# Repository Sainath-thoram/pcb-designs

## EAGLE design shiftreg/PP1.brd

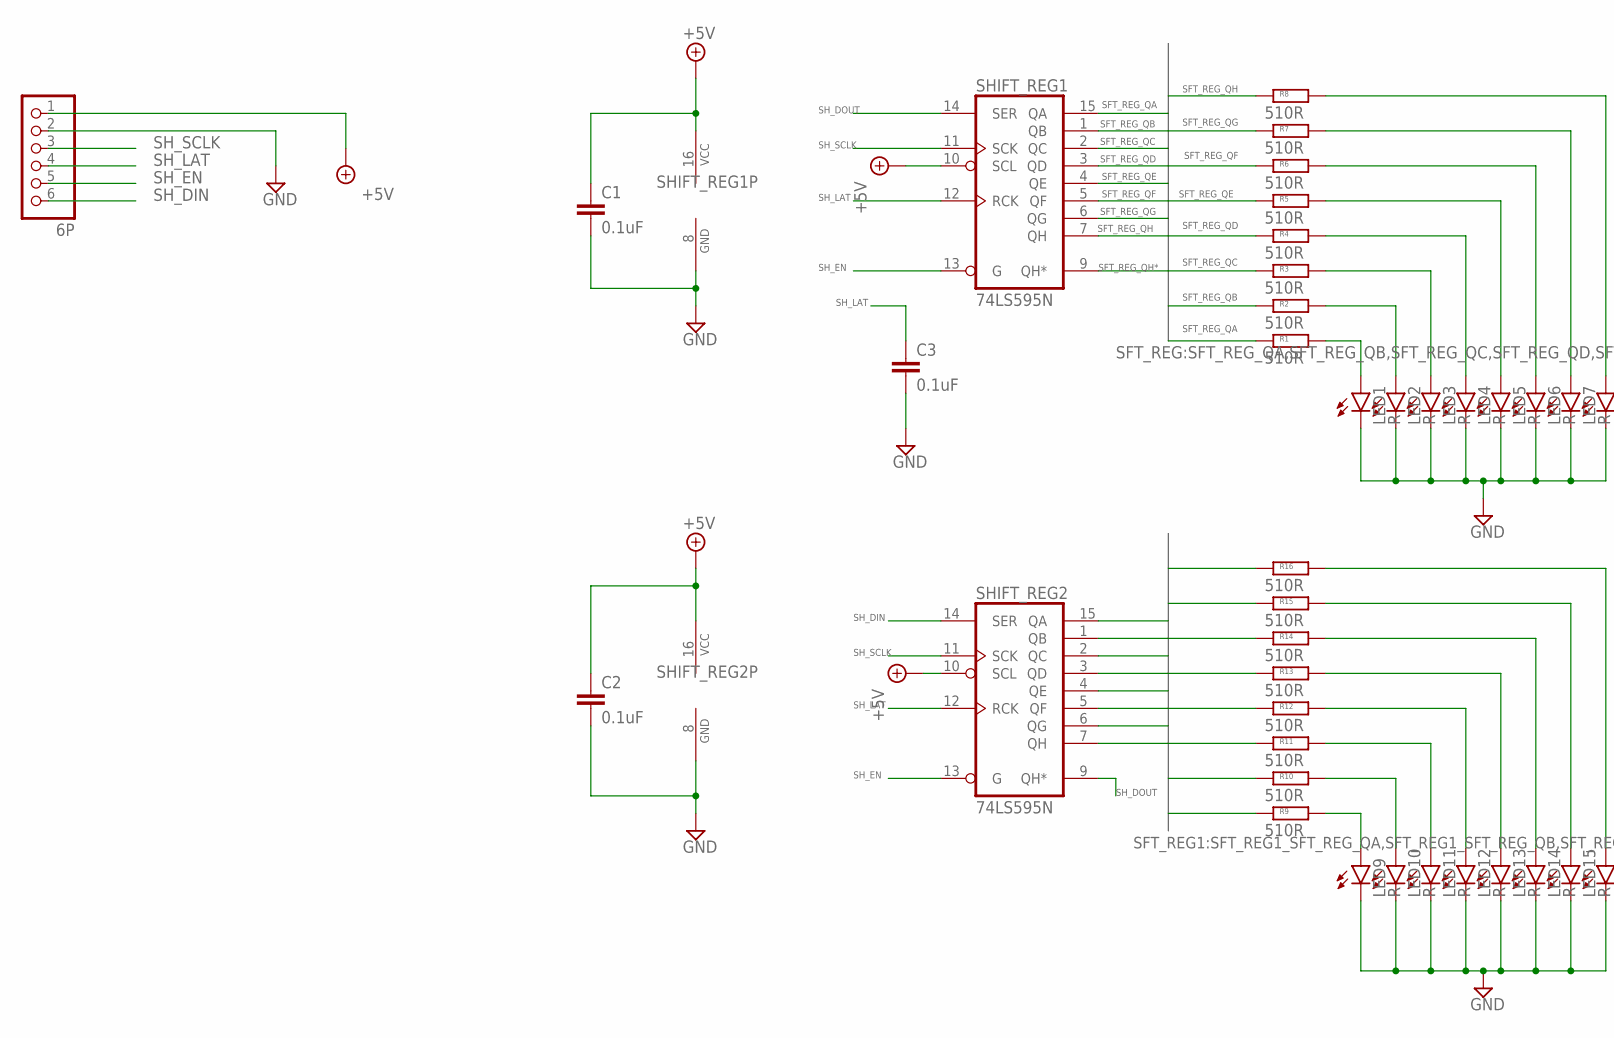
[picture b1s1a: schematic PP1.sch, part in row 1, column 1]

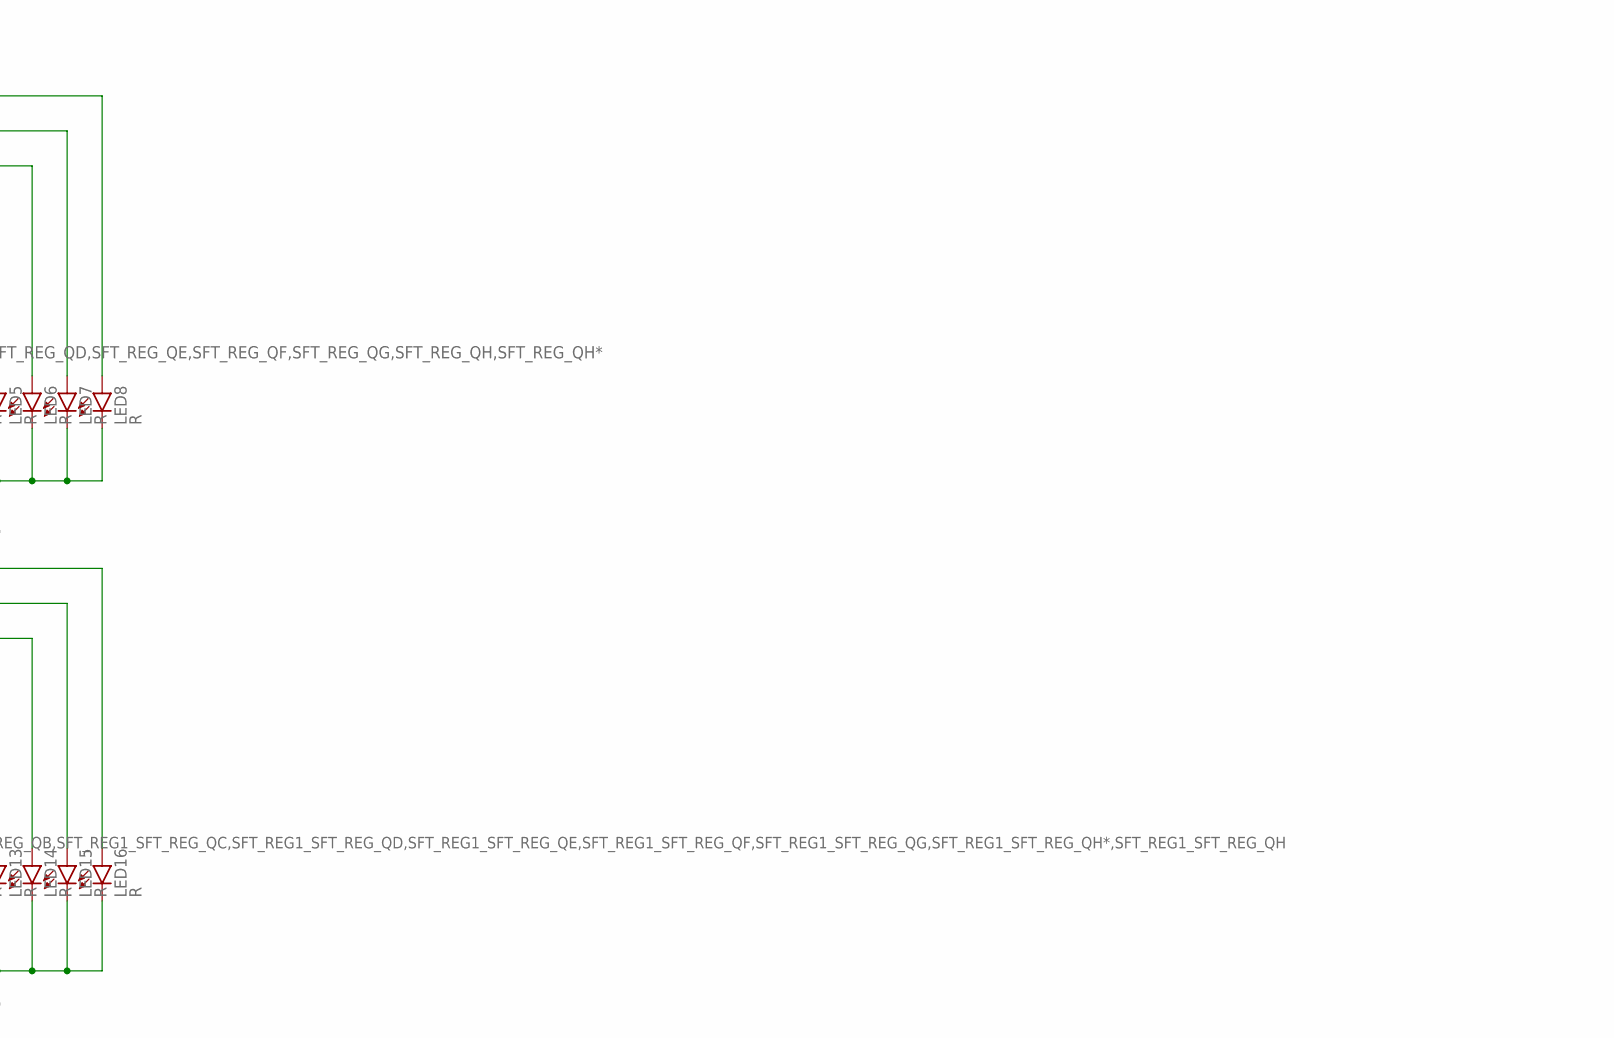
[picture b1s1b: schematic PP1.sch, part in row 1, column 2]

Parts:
C1, C2, C3: 0.1uF; C050-030X075
INPUT: 6P; 1X06/90
LED1, LED2, LED3, LED4, LED5, LED6, LED7, LED8, LED9, LED10, LED11, LED12, LED13, LED14, LED15, LED16: R; LED5MM
R1, R2, R3, R4, R5, R6, R7, R8, R9, R10, R11, R12, R13, R14, R15, R16: 510R; 0207/10
SHIFT_REG1, SHIFT_REG2: 74LS595N; DIL16

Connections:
+5V: C1.1, C2.1, INPUT.1, SHIFT_REG1.10 (SCL), SHIFT_REG1.16 (VCC), SHIFT_REG2.10 (SCL), SHIFT_REG2.16 (VCC)
GND: C1.2, C2.2, C3.2, INPUT.2, LED1.K (C), LED2.K (C), LED3.K (C), LED4.K (C), LED5.K (C), LED6.K (C), LED7.K (C), LED8.K (C), LED9.K (C), LED10.K (C), LED11.K (C), LED12.K (C), LED13.K (C), LED14.K (C), LED15.K (C), LED16.K (C), SHIFT_REG1.8 (GND), SHIFT_REG2.8 (GND)
unnamed: LED1.A, R1.2
unnamed: LED2.A, R2.2
unnamed: LED3.A, R3.2
unnamed: LED4.A, R4.2
unnamed: LED5.A, R5.2
unnamed: LED6.A, R6.2
unnamed: LED9.A, R9.2
unnamed: LED10.A, R10.2
unnamed: LED7.A, R7.2
unnamed: LED8.A, R8.2
unnamed: LED11.A, R11.2
unnamed: LED12.A, R12.2
unnamed: LED13.A, R13.2
unnamed: LED14.A, R14.2
unnamed: LED15.A, R15.2
unnamed: LED16.A, R16.2
SFT_REG1_SFT_REG_QA: R9.1, SHIFT_REG2.15 (QA)
SFT_REG1_SFT_REG_QB: R10.1, SHIFT_REG2.1 (QB)
SFT_REG1_SFT_REG_QC: R11.1, SHIFT_REG2.2 (QC)
SFT_REG1_SFT_REG_QD: R12.1, SHIFT_REG2.3 (QD)
SFT_REG1_SFT_REG_QE: R13.1, SHIFT_REG2.4 (QE)
SFT_REG1_SFT_REG_QF: R14.1, SHIFT_REG2.5 (QF)
SFT_REG1_SFT_REG_QG: R15.1, SHIFT_REG2.6 (QG)
SFT_REG1_SFT_REG_QH: R16.1, SHIFT_REG2.7 (QH)
SFT_REG_QA: R1.1, SHIFT_REG1.15 (QA)
SFT_REG_QB: R2.1, SHIFT_REG1.1 (QB)
SFT_REG_QC: R3.1, SHIFT_REG1.2 (QC)
SFT_REG_QD: R4.1, SHIFT_REG1.3 (QD)
SFT_REG_QE: R5.1, SHIFT_REG1.4 (QE)
SFT_REG_QF: R6.1, SHIFT_REG1.5 (QF)
SFT_REG_QG: R7.1, SHIFT_REG1.6 (QG)
SFT_REG_QH: R8.1, SHIFT_REG1.7 (QH)
SFT_REG_QH*: SHIFT_REG1.9 (QH*)
SH_DIN: INPUT.6, SHIFT_REG2.14 (SER)
SH_DOUT: SHIFT_REG1.14 (SER), SHIFT_REG2.9 (QH*)
SH_EN: INPUT.5, SHIFT_REG1.13 (G), SHIFT_REG2.13 (G)
SH_LAT: C3.1, INPUT.4, SHIFT_REG1.12 (RCK), SHIFT_REG2.12 (RCK)
SH_SCLK: INPUT.3, SHIFT_REG1.11 (SCK), SHIFT_REG2.11 (SCK)

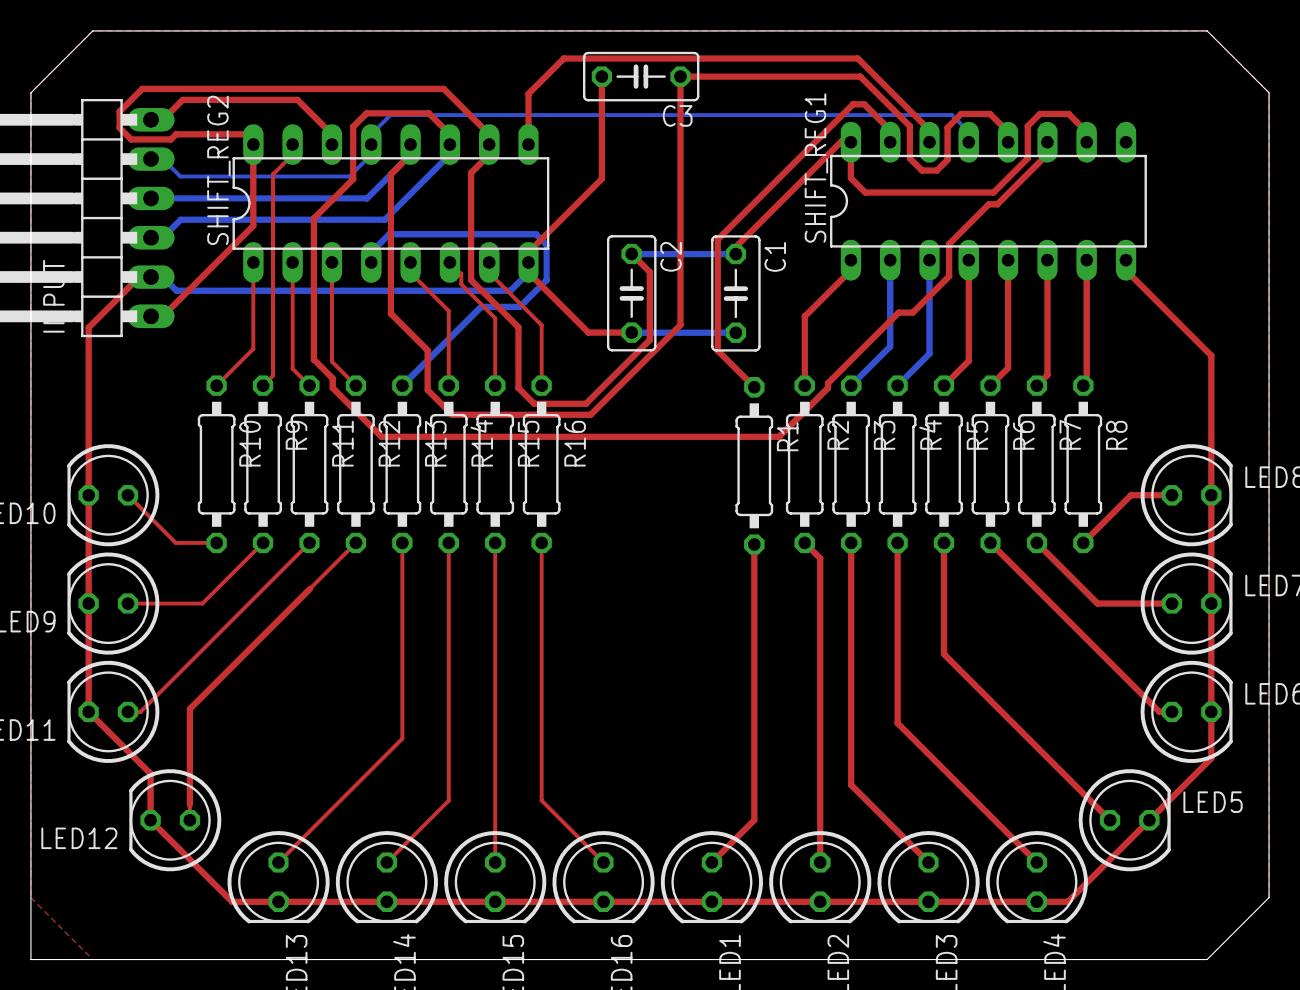
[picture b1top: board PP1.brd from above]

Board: 2 copper layers, 80.0 x 60.0 mm, 38 parts (0 on the bottom side), 39 nets.

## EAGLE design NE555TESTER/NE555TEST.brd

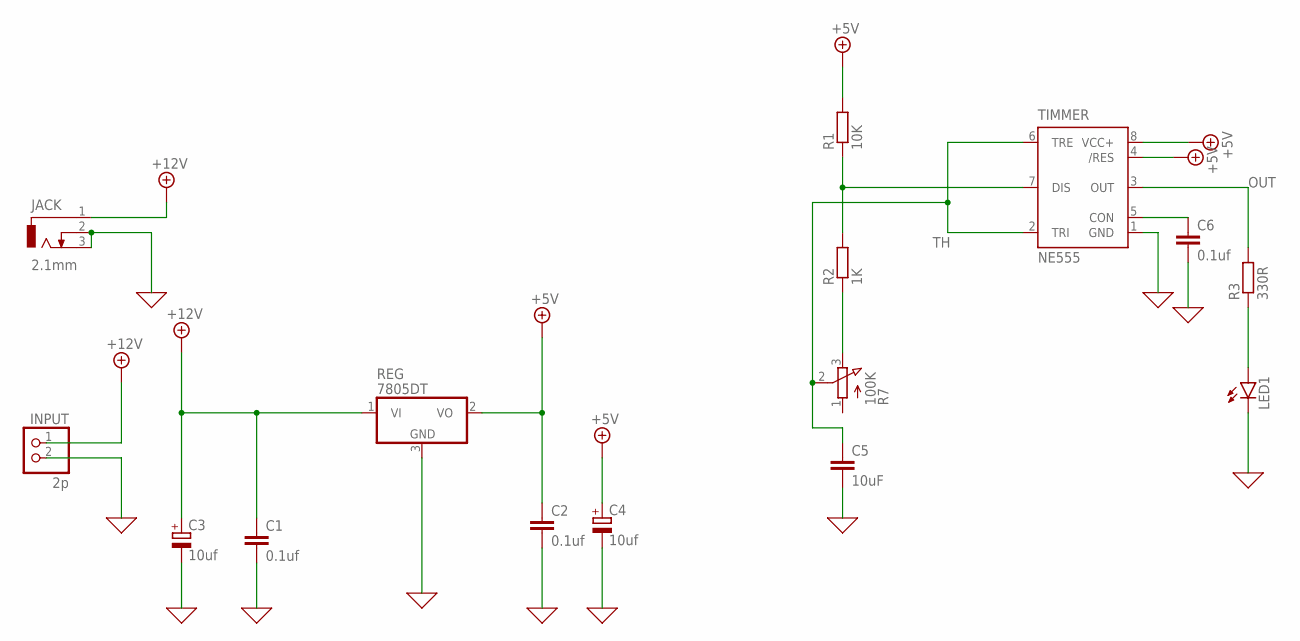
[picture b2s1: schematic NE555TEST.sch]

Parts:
C1, C2, C6: 0.1uf; C050-030X075
C3, C4: 10uf; E3,5-8
C5: 10uF; C050-030X075
INPUT: 2p; 1X02
JACK: 2.1mm; DCJ0202
LED1: LED3MM
R1: 10K; 0207/10
R2: 1K; 0207/10
R3: 330R; 0207/10
R7: 100K; 3RP/1610N
REG: 7805DT; TO252
TIMMER: NE555; DIL-08

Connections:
0: C1.2, C2.2, C3.-, C4.-, C5.2, C6.2, INPUT.2, JACK.2, JACK.3, LED1.K (C), REG.3 (GND), TIMMER.1 (GND)
+5V: C2.1, C4.+, R1.2, REG.2 (VO), TIMMER.4 (/RES), TIMMER.8 (VCC+)
+12V: C1.1, C3.+, INPUT.1, JACK.1, REG.1 (VI)
unnamed: C6.1, TIMMER.5 (CON)
unnamed: R1.1, R2.2, TIMMER.7 (DIS)
unnamed: R2.1, R7.3 (E)
unnamed: LED1.A, R3.1
OUT: R3.2, TIMMER.3 (OUT)
TH: C5.1, R7.2 (S), TIMMER.2 (TRI), TIMMER.6 (TRE)

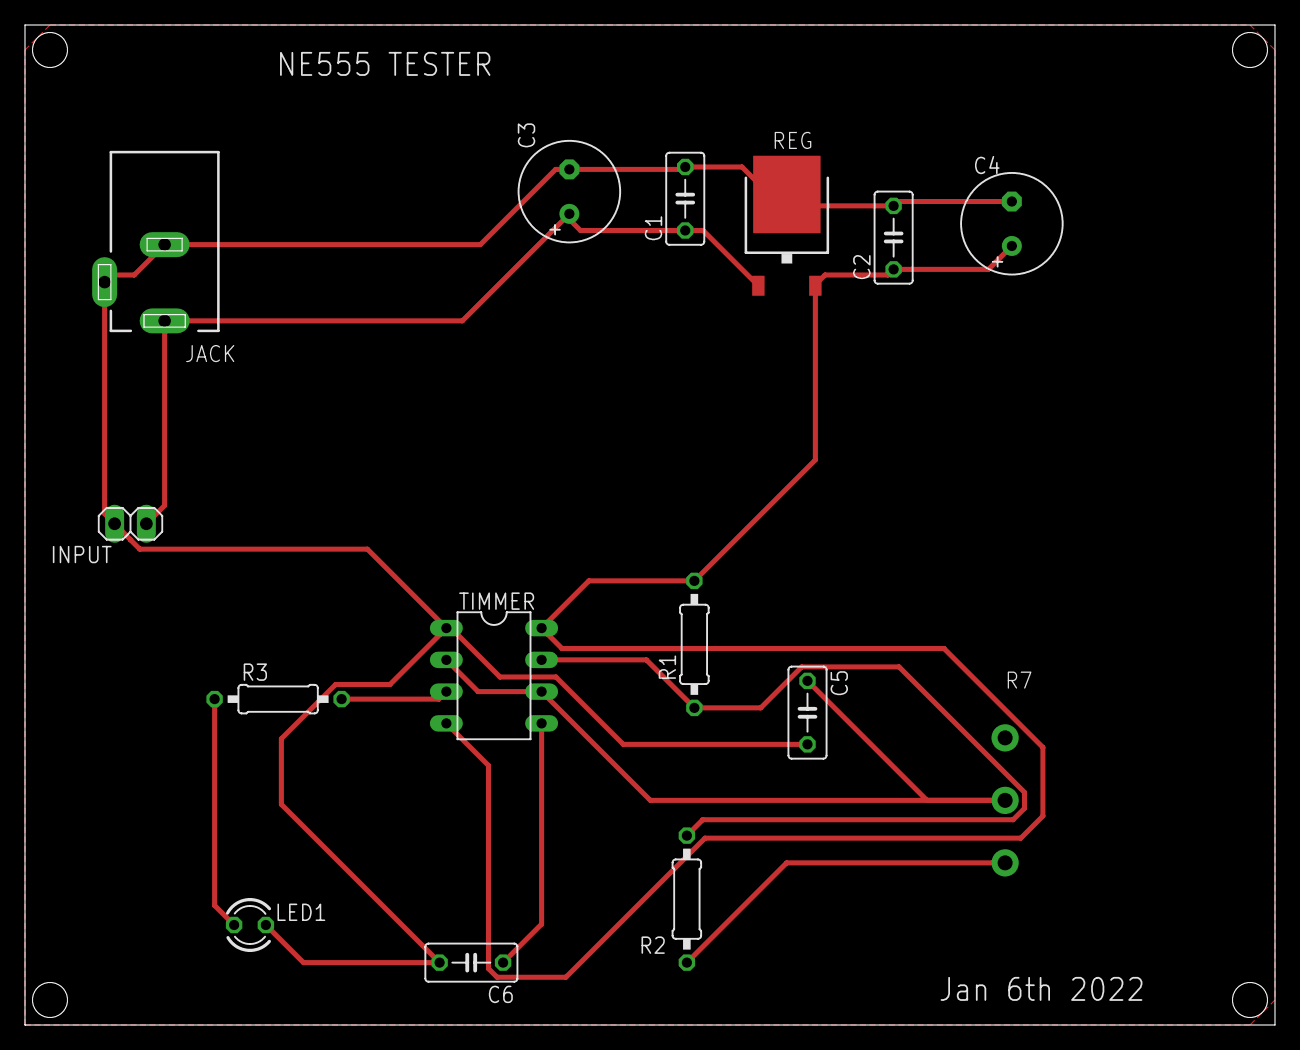
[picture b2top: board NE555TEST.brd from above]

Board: 2 copper layers, 100.0 x 80.0 mm, 15 parts (1 on the bottom side), 9 nets.

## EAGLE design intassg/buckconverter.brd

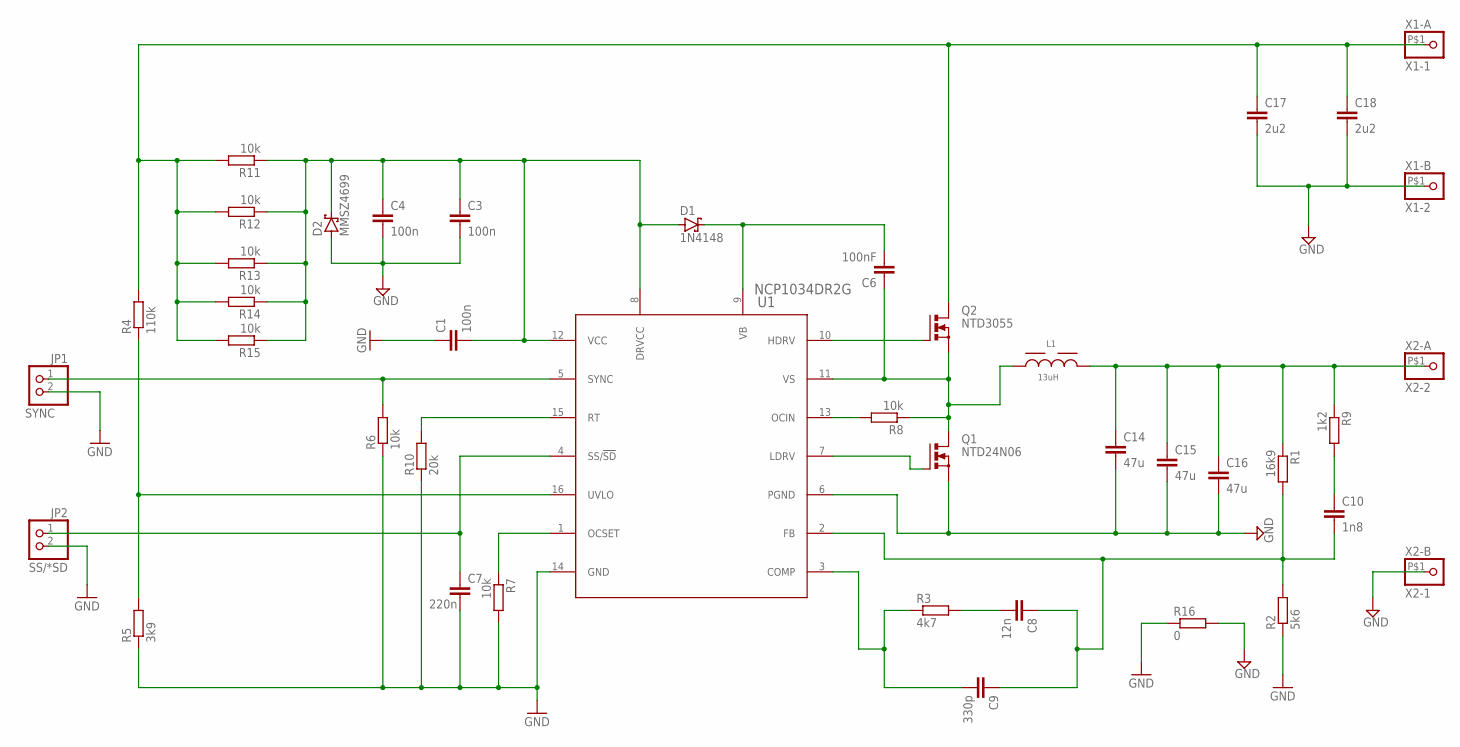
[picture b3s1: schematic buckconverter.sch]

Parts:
C1, C3, C4: 100n; C1206
C6: 100nF; C1206
C7: 220n; C1206
C8: 12n; C1206
C9: 330p; C1206
C10: 1n8; C1206
C14, C15, C16: 47u; C1210
C17, C18: 2u2; C1210
D1: 1N4148; SOT23
D2: MMSZ4699; SOT23
JP1: SYNC; 1X02
JP2: SS/*SD; 1X02
L1: 13uH; WE-HCI_1365
Q1: NTD24N06; TO220BV
Q2: NTD3055; TO220BV
R1: 16k9; R1206
R2: 5k6; R1206
R3: 4k7; R1206
R4: 110k; R1206
R5: 3k9; R1206
R6, R7, R8, R11, R12, R13, R14, R15: 10k; R1206
R9: 1k2; R1206
R10: 20k; R1206
R16: 0; R1206
U1: NCP1034DR2G; SOIC-16_ONS
X1-A: X1-1; 1X1-BIGPOGO
X1-B: X1-2; 1X1-BIGPOGO
X2-A: X2-2; 1X1-BIGPOGO
X2-B: X2-1; 1X1-BIGPOGO

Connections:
GND: C1.1, C3.2, C4.2, C7.2, C14.2, C15.2, C16.2, C17.2, C18.2, D2.1 (A), JP1.2, JP2.2, Q1.S, R2.1, R5.1, R6.1, R7.2, R10.1, R16.1, R16.2, U1.6 (PGND), U1.14 (GND), X1-B.P$1, X2-B.P$1
unnamed: R7.1, U1.1 (OCSET)
unnamed: C7.1, JP2.1, U1.4 (SS/!SD)
unnamed: R10.2, U1.15 (RT)
unnamed: JP1.1, R6.2, U1.5 (SYNC)
unnamed: Q1.G, U1.7 (LDRV)
unnamed: R8.2, U1.13 (OCIN)
unnamed: C6.1, L1.1, Q1.D, Q2.S, R8.1, U1.11 (VS)
unnamed: Q2.G, U1.10 (HDRV)
unnamed: C6.2, D1.3 (C), U1.9 (VB)
unnamed: C10.1, R9.2
unnamed: C8.2, R3.2
unnamed: C8.1, C9.1, C10.2, R1.2, R2.2, U1.2 (FB)
unnamed: C14.1, C15.1, C16.1, L1.2, R1.1, R9.1, X2-A.P$1
unnamed: C9.2, R3.1, U1.3 (COMP)
unnamed: C17.1, C18.1, Q2.D, R4.2, R11.2, R12.2, R13.2, R14.2, R15.2, X1-A.P$1
unnamed: R4.1, R5.2, U1.16 (UVLO)
unnamed: C1.2, C3.1, C4.1, D1.1 (A), D2.3 (C), R11.1, R12.1, R13.1, R14.1, R15.1, U1.8 (DRVCC), U1.12 (VCC)

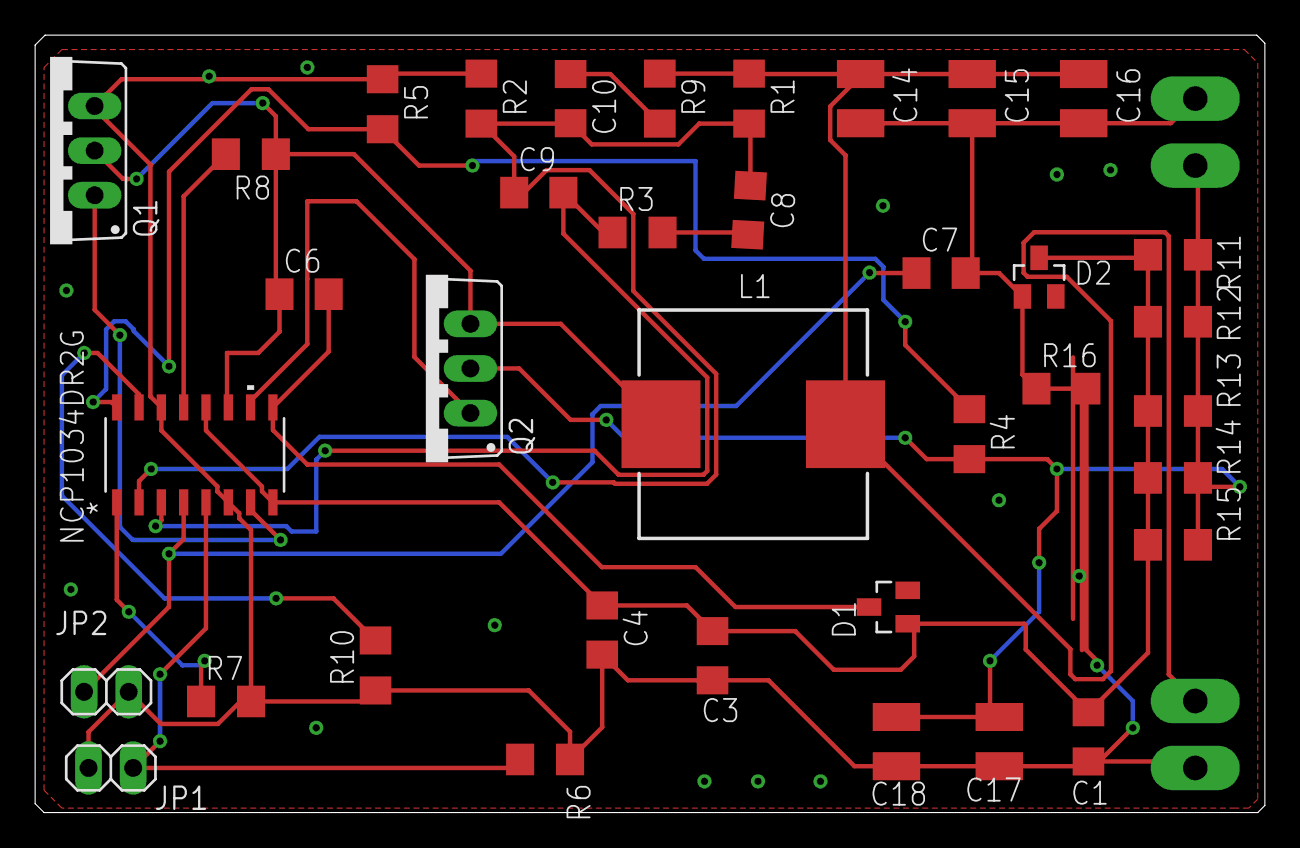
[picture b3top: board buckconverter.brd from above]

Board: 2 copper layers, 70.0 x 44.3 mm, 41 parts (0 on the bottom side), 18 nets.

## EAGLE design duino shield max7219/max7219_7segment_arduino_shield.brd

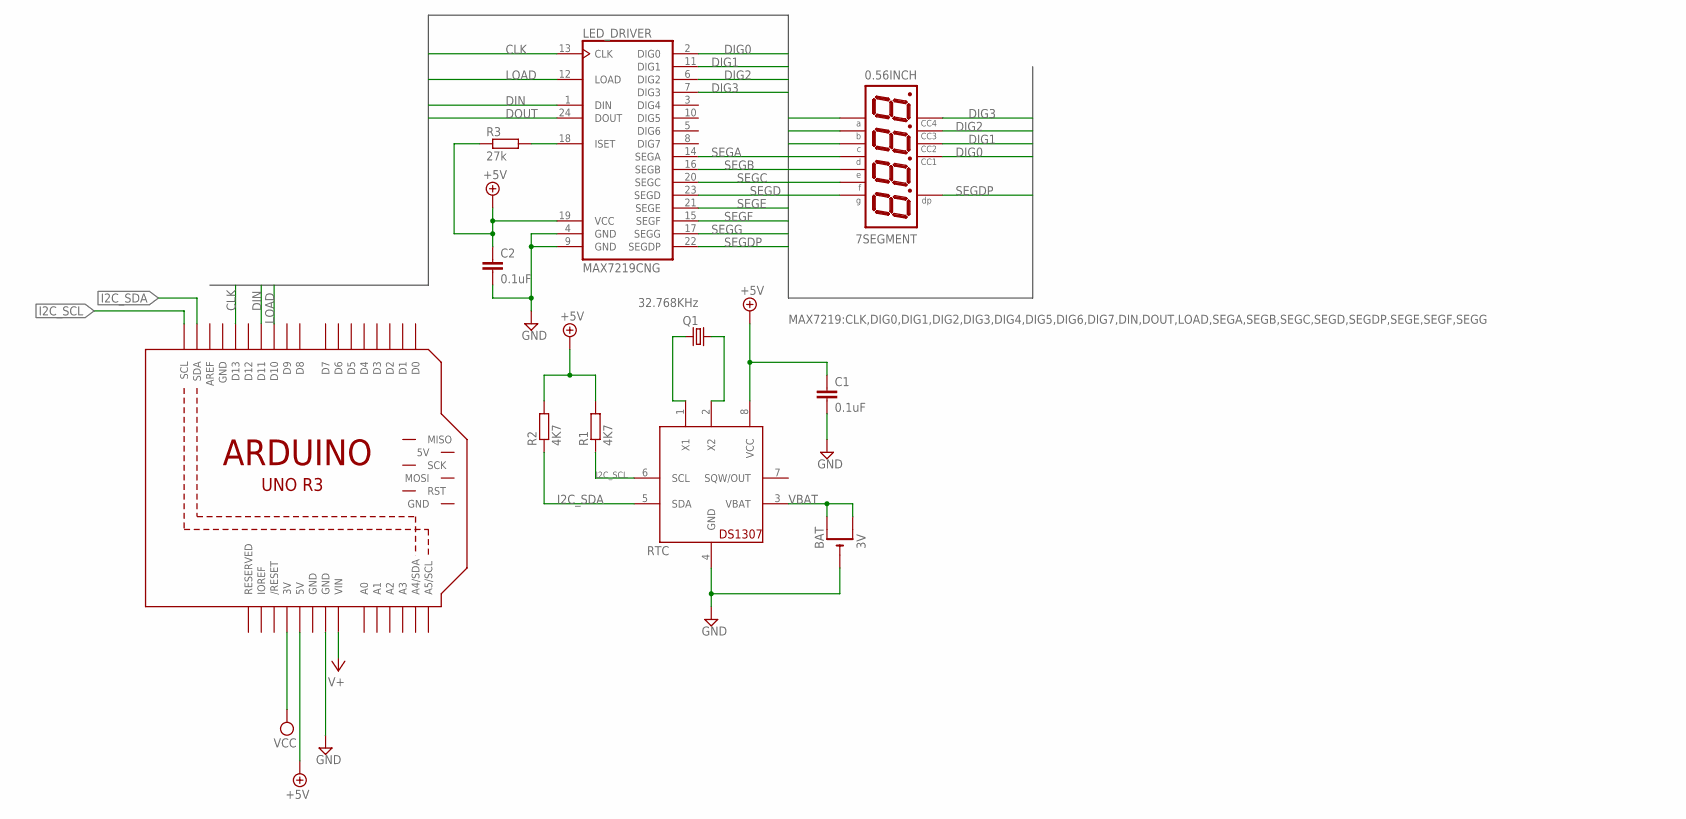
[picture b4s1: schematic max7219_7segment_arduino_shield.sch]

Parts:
7SEGMENT: 0.56INCH; NFD-5641
BAT: 3V; CR1220-SMD
C1, C2: 0.1uF; C050-030X075
LED_DRIVER: MAX7219CNG; DIL24-3
M1: ARDUINO_R3_ICSP; ARDUINOR3_ICSP
Q1: 32.768KHz; TC26V
R1, R2: 4K7; M1206
R3: 27k; M1206
RTC: DS1307; DIL08

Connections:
+5V: C1.1, C2.1, LED_DRIVER.19 (VCC), M1.5V, R1.2, R2.2, R3.1, RTC.8 (VCC)
CLK: LED_DRIVER.13 (CLK), M1.D13
DIG0: 7SEGMENT.P$12, LED_DRIVER.2 (DIG0)
DIG1: 7SEGMENT.P$9, LED_DRIVER.11 (DIG1)
DIG2: 7SEGMENT.P$8, LED_DRIVER.6 (DIG2)
DIG3: 7SEGMENT.P$6, LED_DRIVER.7 (DIG3)
DIN: LED_DRIVER.1 (DIN), M1.D11
DOUT: LED_DRIVER.24 (DOUT)
GND: BAT.-, C1.2, C2.2, LED_DRIVER.4 (GND), LED_DRIVER.9 (GND), M1.GND, M1.GND@1 (GND), M1.GND@3 (GND), RTC.4 (GND)
I2C_SCL: M1.SCL, R1.1, RTC.6 (SCL)
I2C_SDA: M1.SDA, R2.1, RTC.5 (SDA)
LOAD: LED_DRIVER.12 (LOAD), M1.D10
unnamed: LED_DRIVER.18 (ISET), R3.2
unnamed: Q1.1, RTC.2 (X2)
unnamed: Q1.2, RTC.1 (X1)
SEGA: 7SEGMENT.P$11, LED_DRIVER.14 (SEGA)
SEGB: 7SEGMENT.P$7, LED_DRIVER.16 (SEGB)
SEGC: 7SEGMENT.P$4, LED_DRIVER.20 (SEGC)
SEGD: 7SEGMENT.P$2, LED_DRIVER.23 (SEGD)
SEGDP: 7SEGMENT.P$3, LED_DRIVER.22 (SEGDP)
SEGE: 7SEGMENT.P$1, LED_DRIVER.21 (SEGE)
SEGF: 7SEGMENT.P$10, LED_DRIVER.15 (SEGF)
SEGG: 7SEGMENT.P$5, LED_DRIVER.17 (SEGG)
V+: M1.VIN
VBAT: BAT.+$1 (+), BAT.+$2 (+1), RTC.3 (VBAT)
VCC: M1.3V

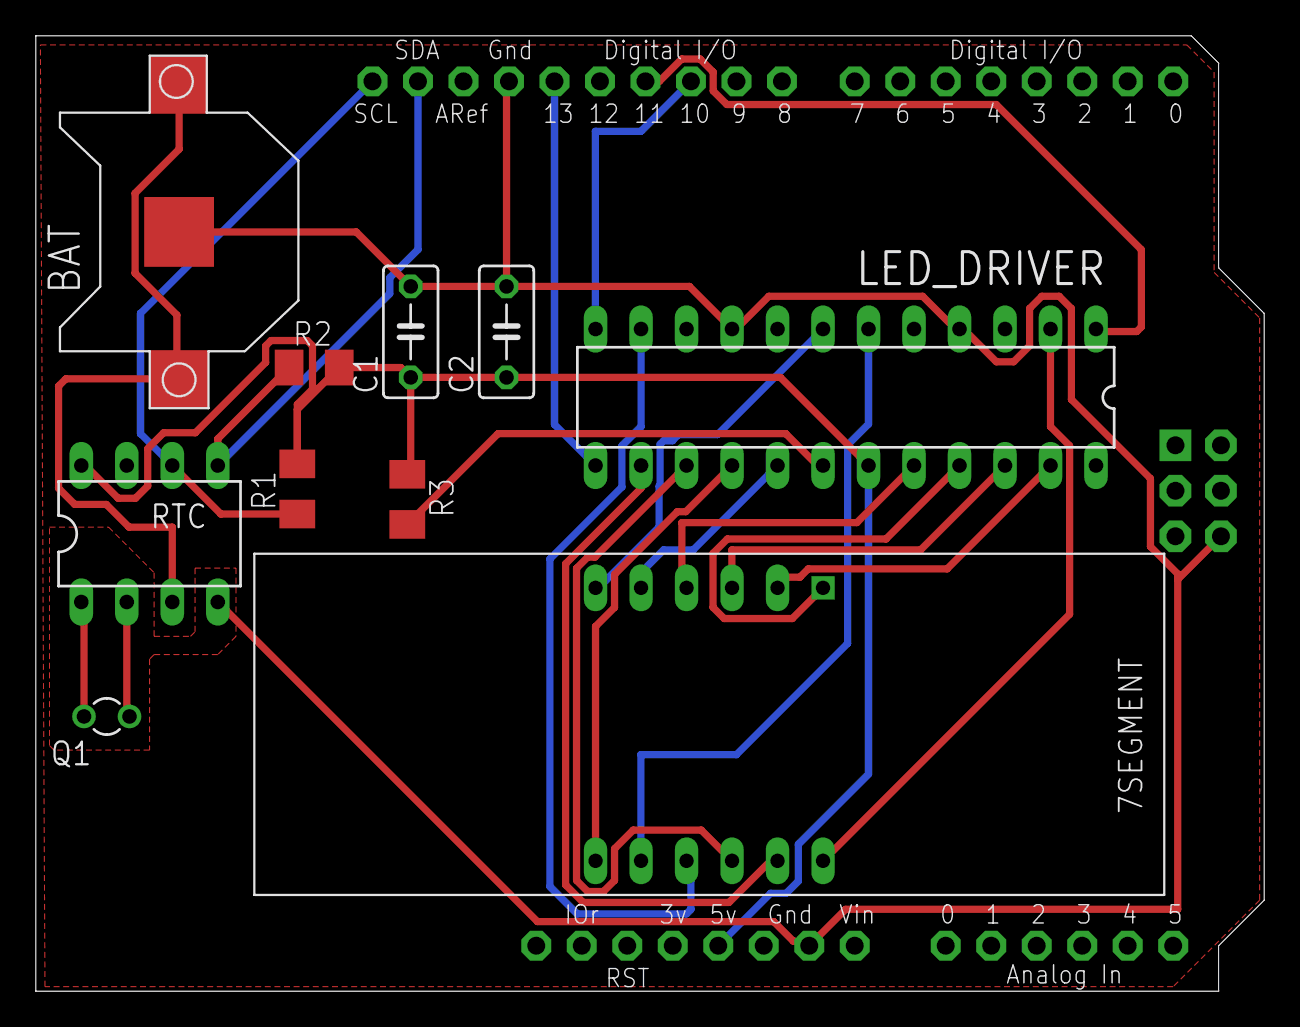
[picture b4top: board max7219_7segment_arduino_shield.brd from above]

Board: 2 copper layers, 68.6 x 53.3 mm, 11 parts (0 on the bottom side), 23 nets.

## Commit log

2023-08-17 Create buck converter

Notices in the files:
parts and their libraries:
Wurth_Power Magnetics_WE-HCI: Copyright: Würth Elektronik
COPYRIGHT: Copyright (C) 2022 Ultra Librarian. All rights reserved.
